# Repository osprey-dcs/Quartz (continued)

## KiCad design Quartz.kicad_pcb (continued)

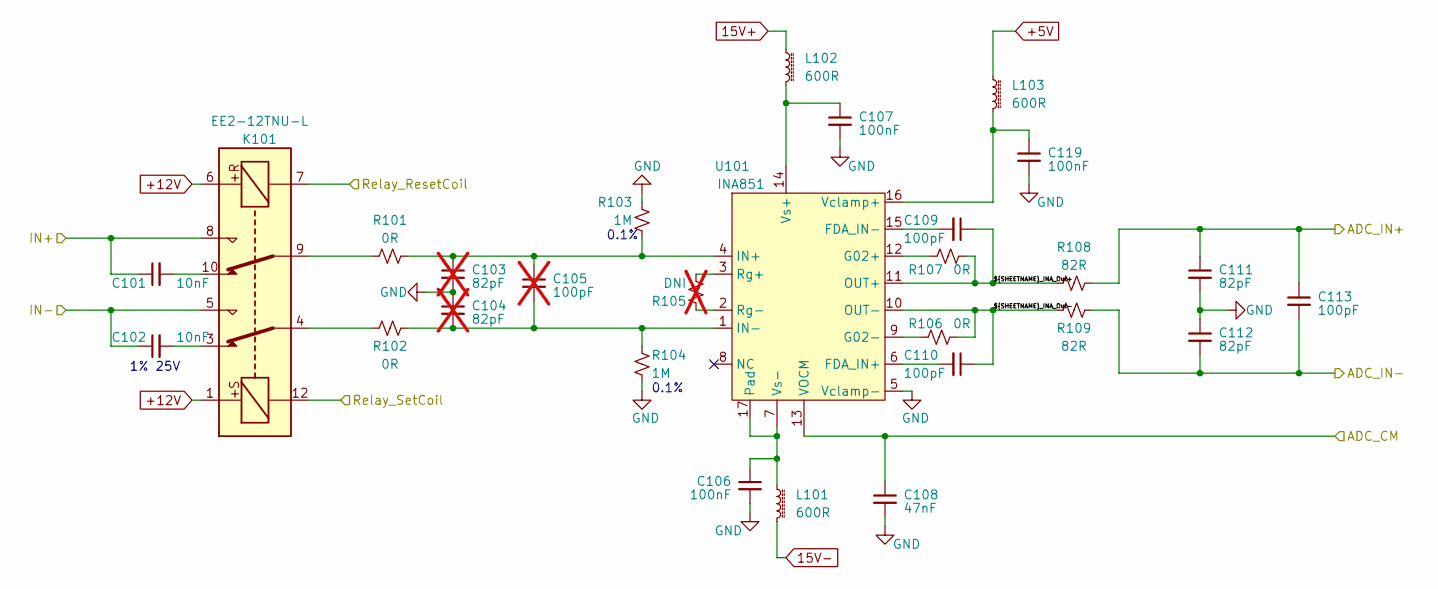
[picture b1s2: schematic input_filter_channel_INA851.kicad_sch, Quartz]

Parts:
C101, C102: 10nF; C_0603_1608Metric; MPN C0603C103F3GAC7867
C103, C104: 82pF; C_0402_1005Metric; MPN DNI; not fitted
C105: 100pF; C_0402_1005Metric; MPN DNI; not fitted
C106, C107, C119: 100nF; C_0402_1005Metric; MPN CL05A104KA5NNNC
C108: 47nF; C_0402_1005Metric; MPN CGA2B3X7R1H473K050BB
C109, C110, C113: 100pF; C_0402_1005Metric; MPN GRM1555C1H101JA01D
C111, C112: 82pF; C_0402_1005Metric; MPN CC0402JRNPO9BN820
K101: EE2-12TNU-L; Relay_DPDT_Kemet_EE2_NU_DoubleCoil; MPN EE2-12TNU-L
L101, L102, L103: 600R; L_0402_1005Metric; MPN BLM15AX601SN1D
R101, R102, R106, R107: 0R; R_0603_1608Metric; MPN ERJ-2GE0R00X
R103, R104: 1M; R_0603_1608Metric; MPN CPF0603B1M0E1
R105: DNI; R_0402_1005Metric; MPN TNPW040211K8BEED; not fitted
R108, R109: 82R; R_0402_1005Metric; MPN RC0402FR-0782RL
U101: INA851; QFN-16-1EP_3x3mm_P0.5mm_EP1.75x1.75mm_ThermalVias; MPN INA851RGTR

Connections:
15V+: L102.1; also elsewhere on the board
15V-: L101.2; also elsewhere on the board
+5V: L103.1; also elsewhere on the board
+12V: K101.1, K101.6; also elsewhere on the board
/ADC1/AIN3+: C111.1, C113.1, R108.2; also elsewhere on the board
/ADC1/AIN3-: C112.2, C113.2, R109.2; also elsewhere on the board
/ADC_VCM1: C108.1, U101.13 (VOCM); also elsewhere on the board
/AIN1+: C101.1, K101.8; also elsewhere on the board
/AIN1-: C102.1, K101.5; also elsewhere on the board
/Channel01/Channel01_INA_Out+: C109.1, R107.2, R108.1, U101.11 (OUT+)
/Channel01/Channel01_INA_Out-: C110.1, R106.2, R109.1, U101.10 (OUT-)
/Relay_ResetCoil1: K101.7; also elsewhere on the board
/Relay_SetCoil1: K101.12; also elsewhere on the board
GND: C103.2, C104.1, C106.2, C107.2, C108.2, C111.2, C112.1, C119.2, R103.1, R104.1, U101.5 (Vclamp-); also elsewhere on the board
unnamed: C101.2, K101.10
unnamed: C102.2, K101.3
unnamed: K101.4, R102.1
unnamed: K101.9, R101.1
unnamed: C110.2, U101.6 (FDA_IN+)
unnamed: C109.2, U101.15 (FDA_IN-)
unnamed: R107.1, U101.12 (G02+)
unnamed: R106.1, U101.9 (G02-)
unnamed: C103.1, C105.1, R101.2, R103.2, U101.4 (IN+)
unnamed: C104.2, C105.2, R102.2, R104.2, U101.1 (IN-)
unnamed: R105.1, U101.3 (Rg+)
unnamed: R105.2, U101.2 (Rg-)
unnamed: C119.1, L103.2, U101.16 (Vclamp+)
unnamed: C107.1, L102.2, U101.14 (Vs+)
unnamed: C106.1, L101.1, U101.7 (Vs-), U101.17 (Pad)

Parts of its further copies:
C201, C202, C301, C302, C401, C402, C501, C502, C601, C602, C701, C702, C801, C802, C901, C902, C1001, C1002, C1101, C1102, C1201, C1202, C1301, C1302, C1401, C1402, C1501, C1502, C1601, C1602, C1701, C1702, C1801, C1802, C1901, C1902, C2001, C2002, C2101, C2102, C2201, C2202, C2301, C2302, C2401, C2402, C2501, C2502, C2601, C2602, C2701, C2702, C2801, C2802, C2901, C2902, C3001, C3002, C3101, C3102, C3201, C3202: 10nF; C_0603_1608Metric; MPN C0603C103F3GAC7867
C203, C204, C303, C304, C403, C404, C503, C504, C603, C604, C703, C704, C803, C804, C903, C904, C1003, C1004, C1103, C1104, C1203, C1204, C1303, C1304, C1403, C1404, C1503, C1504, C1603, C1604, C1703, C1704, C1803, C1804, C1903, C1904, C2003, C2004, C2103, C2104, C2203, C2204, C2303, C2304, C2403, C2404, C2503, C2504, C2603, C2604, C2703, C2704, C2803, C2804, C2903, C2904, C3003, C3004, C3103, C3104, C3203, C3204: 82pF; C_0402_1005Metric; MPN DNI; not fitted
C205, C305, C405, C505, C605, C705, C805, C905, C1005, C1105, C1205, C1305, C1405, C1505, C1605, C1705, C1805, C1905, C2005, C2105, C2205, C2305, C2405, C2505, C2605, C2705, C2805, C2905, C3005, C3105, C3205: 100pF; C_0402_1005Metric; MPN DNI; not fitted
C206, C207, C214, C306, C307, C314, C406, C407, C414, C506, C507, C514, C606, C607, C614, C706, C707, C714, C806, C807, C814, C906, C907, C914, C1006, C1007, C1014, C1106, C1107, C1114, C1206, C1207, C1214, C1306, C1307, C1314, C1406, C1407, C1414, C1506, C1507, C1514, C1606, C1607, C1614, C1706, C1707, C1714, C1806, C1807, C1814, C1906, C1907, C1914, C2006, C2007, C2014, C2106, C2107, C2114, C2206, C2207, C2214, C2306, C2307, C2314, C2406, C2407, C2414, C2506, C2507, C2514, C2606, C2607, C2614, C2706, C2707, C2714, C2806, C2807, C2814, C2906, C2907, C2914, C3006, C3007, C3014, C3106, C3107, C3114, C3206, C3207, C3214: 100nF; C_0402_1005Metric; MPN CL05A104KA5NNNC
C208, C308, C408, C508, C608, C708, C808, C908, C1008, C1108, C1208, C1308, C1408, C1508, C1608, C1708, C1808, C1908, C2008, C2108, C2208, C2308, C2408, C2508, C2608, C2708, C2808, C2908, C3008, C3108, C3208: 47nF; C_0402_1005Metric; MPN CGA2B3X7R1H473K050BB
C209, C210, C213, C309, C310, C313, C409, C410, C413, C509, C510, C513, C609, C610, C613, C709, C710, C713, C809, C810, C813, C909, C910, C913, C1009, C1010, C1013, C1109, C1110, C1113, C1209, C1210, C1213, C1309, C1310, C1313, C1409, C1410, C1413, C1509, C1510, C1513, C1609, C1610, C1613, C1709, C1710, C1713, C1809, C1810, C1813, C1909, C1910, C1913, C2009, C2010, C2013, C2109, C2110, C2113, C2209, C2210, C2213, C2309, C2310, C2313, C2409, C2410, C2413, C2509, C2510, C2513, C2609, C2610, C2613, C2709, C2710, C2713, C2809, C2810, C2813, C2909, C2910, C2913, C3009, C3010, C3013, C3109, C3110, C3113, C3209, C3210, C3213: 100pF; C_0402_1005Metric; MPN GRM1555C1H101JA01D
C211, C212, C311, C312, C411, C412, C511, C512, C611, C612, C711, C712, C811, C812, C911, C912, C1011, C1012, C1111, C1112, C1211, C1212, C1311, C1312, C1411, C1412, C1511, C1512, C1611, C1612, C1711, C1712, C1811, C1812, C1911, C1912, C2011, C2012, C2111, C2112, C2211, C2212, C2311, C2312, C2411, C2412, C2511, C2512, C2611, C2612, C2711, C2712, C2811, C2812, C2911, C2912, C3011, C3012, C3111, C3112, C3211, C3212: 82pF; C_0402_1005Metric; MPN CC0402JRNPO9BN820
K201, K301, K401, K501, K601, K701, K801, K901, K1001, K1101, K1201, K1301, K1401, K1501, K1601, K1701, K1801, K1901, K2001, K2101, K2201, K2301, K2401, K2501, K2601, K2701, K2801, K2901, K3001, K3101, K3201: EE2-12TNU-L; Relay_DPDT_Kemet_EE2_NU_DoubleCoil; MPN EE2-12TNU-L
L201, L202, L203, L301, L302, L303, L401, L402, L403, L501, L502, L503, L601, L602, L603, L701, L702, L703, L801, L802, L803, L901, L902, L903, L1001, L1002, L1003, L1101, L1102, L1103, L1201, L1202, L1203, L1301, L1302, L1303, L1401, L1402, L1403, L1501, L1502, L1503, L1601, L1602, L1603, L1701, L1702, L1703, L1801, L1802, L1803, L1901, L1902, L1903, L2001, L2002, L2003, L2101, L2102, L2103, L2201, L2202, L2203, L2301, L2302, L2303, L2401, L2402, L2403, L2501, L2502, L2503, L2601, L2602, L2603, L2701, L2702, L2703, L2801, L2802, L2803, L2901, L2902, L2903, L3001, L3002, L3003, L3101, L3102, L3103, L3201, L3202, L3203: 600R; L_0402_1005Metric; MPN BLM15AX601SN1D
R201, R202, R206, R207, R301, R302, R306, R307, R401, R402, R406, R407, R501, R502, R506, R507, R601, R602, R606, R607, R701, R702, R706, R707, R801, R802, R806, R807, R901, R902, R906, R907, R1001, R1002, R1006, R1007, R1101, R1102, R1106, R1107, R1201, R1202, R1206, R1207, R1301, R1302, R1306, R1307, R1401, R1402, R1406, R1407, R1501, R1502, R1506, R1507, R1601, R1602, R1606, R1607, R1701, R1702, R1706, R1707, R1801, R1802, R1806, R1807, R1901, R1902, R1906, R1907, R2001, R2002, R2006, R2007, R2101, R2102, R2106, R2107, R2201, R2202, R2206, R2207, R2301, R2302, R2306, R2307, R2401, R2402, R2406, R2407, R2501, R2502, R2506, R2507, R2601, R2602, R2606, R2607, R2701, R2702, R2706, R2707, R2801, R2802, R2806, R2807, R2901, R2902, R2906, R2907, R3001, R3002, R3006, R3007, R3101, R3102, R3106, R3107, R3201, R3202, R3206, R3207: 0R; R_0603_1608Metric; MPN ERJ-2GE0R00X
R203, R204, R303, R304, R403, R404, R503, R504, R603, R604, R703, R704, R803, R804, R903, R904, R1003, R1004, R1103, R1104, R1203, R1204, R1303, R1304, R1403, R1404, R1503, R1504, R1603, R1604, R1703, R1704, R1803, R1804, R1903, R1904, R2003, R2004, R2103, R2104, R2203, R2204, R2303, R2304, R2403, R2404, R2503, R2504, R2603, R2604, R2703, R2704, R2803, R2804, R2903, R2904, R3003, R3004, R3103, R3104, R3203, R3204: 1M; R_0603_1608Metric; MPN CPF0603B1M0E1
R205, R305, R405, R505, R605, R705, R805, R905, R1005, R1105, R1205, R1305, R1405, R1505, R1605, R1705, R1805, R1905, R2005, R2105, R2205, R2305, R2405, R2505, R2605, R2705, R2805, R2905, R3005, R3105, R3205: DNI; R_0402_1005Metric; MPN TNPW040211K8BEED; not fitted
R208, R209, R308, R309, R408, R409, R508, R509, R608, R609, R708, R709, R808, R809, R908, R909, R1008, R1009, R1108, R1109, R1208, R1209, R1308, R1309, R1408, R1409, R1508, R1509, R1608, R1609, R1708, R1709, R1808, R1809, R1908, R1909, R2008, R2009, R2108, R2109, R2208, R2209, R2308, R2309, R2408, R2409, R2508, R2509, R2608, R2609, R2708, R2709, R2808, R2809, R2908, R2909, R3008, R3009, R3108, R3109, R3208, R3209: 82R; R_0402_1005Metric; MPN RC0402FR-0782RL
U201, U301, U401, U501, U601, U701, U801, U901, U1001, U1101, U1201, U1301, U1401, U1501, U1601, U1701, U1801, U1901, U2001, U2101, U2201, U2301, U2401, U2501, U2601, U2701, U2801, U2901, U3001, U3101, U3201: INA851; QFN-16-1EP_3x3mm_P0.5mm_EP1.75x1.75mm_ThermalVias; MPN INA851RGTR

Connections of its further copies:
15V+: L202.1, L302.1, L402.1, L502.1, L602.1, L702.1, L802.1, L902.1, L1002.1, L1102.1, L1202.1, L1302.1, L1402.1, L1502.1, L1602.1, L1702.1, L1802.1, L1902.1, L2002.1, L2102.1, L2202.1, L2302.1, L2402.1, L2502.1, L2602.1, L2702.1, L2802.1, L2902.1, L3002.1, L3102.1, L3202.1; also elsewhere on the board
15V-: L201.2, L301.2, L401.2, L501.2, L601.2, L701.2, L801.2, L901.2, L1001.2, L1101.2, L1201.2, L1301.2, L1401.2, L1501.2, L1601.2, L1701.2, L1801.2, L1901.2, L2001.2, L2101.2, L2201.2, L2301.2, L2401.2, L2501.2, L2601.2, L2701.2, L2801.2, L2901.2, L3001.2, L3101.2, L3201.2; also elsewhere on the board
+5V: L203.1, L303.1, L403.1, L503.1, L603.1, L703.1, L803.1, L903.1, L1003.1, L1103.1, L1203.1, L1303.1, L1403.1, L1503.1, L1603.1, L1703.1, L1803.1, L1903.1, L2003.1, L2103.1, L2203.1, L2303.1, L2403.1, L2503.1, L2603.1, L2703.1, L2803.1, L2903.1, L3003.1, L3103.1, L3203.1; also elsewhere on the board
+12V: K201.1, K201.6, K301.1, K301.6, K401.1, K401.6, K501.1, K501.6, K601.1, K601.6, K701.1, K701.6, K801.1, K801.6, K901.1, K901.6, K1001.1, K1001.6, K1101.1, K1101.6, K1201.1, K1201.6, K1301.1, K1301.6, K1401.1, K1401.6, K1501.1, K1501.6, K1601.1, K1601.6, K1701.1, K1701.6, K1801.1, K1801.6, K1901.1, K1901.6, K2001.1, K2001.6, K2101.1, K2101.6, K2201.1, K2201.6, K2301.1, K2301.6, K2401.1, K2401.6, K2501.1, K2501.6, K2601.1, K2601.6, K2701.1, K2701.6, K2801.1, K2801.6, K2901.1, K2901.6, K3001.1, K3001.6, K3101.1, K3101.6, K3201.1, K3201.6; also elsewhere on the board
/ADC1/AIN0+: C411.1, C413.1, R408.2; also elsewhere on the board
/ADC1/AIN0-: C412.2, C413.2, R409.2; also elsewhere on the board
/ADC1/AIN1+: C311.1, C313.1, R308.2; also elsewhere on the board
/ADC1/AIN1-: C312.2, C313.2, R309.2; also elsewhere on the board
/ADC1/AIN2+: C211.1, C213.1, R208.2; also elsewhere on the board
/ADC1/AIN2-: C212.2, C213.2, R209.2; also elsewhere on the board
/ADC1/AIN4+: C511.1, C513.1, R508.2; also elsewhere on the board
/ADC1/AIN4-: C512.2, C513.2, R509.2; also elsewhere on the board
/ADC1/AIN5+: C611.1, C613.1, R608.2; also elsewhere on the board
/ADC1/AIN5-: C612.2, C613.2, R609.2; also elsewhere on the board
/ADC1/AIN6+: C711.1, C713.1, R708.2; also elsewhere on the board
/ADC1/AIN6-: C712.2, C713.2, R709.2; also elsewhere on the board
/ADC1/AIN7+: C811.1, C813.1, R808.2; also elsewhere on the board
/ADC1/AIN7-: C812.2, C813.2, R809.2; also elsewhere on the board
/ADC2/AIN0+: C1211.1, C1213.1, R1208.2; also elsewhere on the board
/ADC2/AIN0-: C1212.2, C1213.2, R1209.2; also elsewhere on the board
/ADC2/AIN1+: C1111.1, C1113.1, R1108.2; also elsewhere on the board
/ADC2/AIN1-: C1112.2, C1113.2, R1109.2; also elsewhere on the board
/ADC2/AIN2+: C1011.1, C1013.1, R1008.2; also elsewhere on the board
/ADC2/AIN2-: C1012.2, C1013.2, R1009.2; also elsewhere on the board
/ADC2/AIN3+: C911.1, C913.1, R908.2; also elsewhere on the board
/ADC2/AIN3-: C912.2, C913.2, R909.2; also elsewhere on the board
/ADC2/AIN4+: C1311.1, C1313.1, R1308.2; also elsewhere on the board
/ADC2/AIN4-: C1312.2, C1313.2, R1309.2; also elsewhere on the board
/ADC2/AIN5+: C1411.1, C1413.1, R1408.2; also elsewhere on the board
/ADC2/AIN5-: C1412.2, C1413.2, R1409.2; also elsewhere on the board
/ADC2/AIN6+: C1511.1, C1513.1, R1508.2; also elsewhere on the board
/ADC2/AIN6-: C1512.2, C1513.2, R1509.2; also elsewhere on the board
/ADC2/AIN7+: C1611.1, C1613.1, R1608.2; also elsewhere on the board
/ADC2/AIN7-: C1612.2, C1613.2, R1609.2; also elsewhere on the board
/ADC3/AIN0+: C2011.1, C2013.1, R2008.2; also elsewhere on the board
/ADC3/AIN0-: C2012.2, C2013.2, R2009.2; also elsewhere on the board
/ADC3/AIN1+: C1911.1, C1913.1, R1908.2; also elsewhere on the board
/ADC3/AIN1-: C1912.2, C1913.2, R1909.2; also elsewhere on the board
/ADC3/AIN2+: C1811.1, C1813.1, R1808.2; also elsewhere on the board
/ADC3/AIN2-: C1812.2, C1813.2, R1809.2; also elsewhere on the board
/ADC3/AIN3+: C1711.1, C1713.1, R1708.2; also elsewhere on the board
/ADC3/AIN3-: C1712.2, C1713.2, R1709.2; also elsewhere on the board
/ADC3/AIN4+: C2111.1, C2113.1, R2108.2; also elsewhere on the board
/ADC3/AIN4-: C2112.2, C2113.2, R2109.2; also elsewhere on the board
/ADC3/AIN5+: C2211.1, C2213.1, R2208.2; also elsewhere on the board
/ADC3/AIN5-: C2212.2, C2213.2, R2209.2; also elsewhere on the board
/ADC3/AIN6+: C2311.1, C2313.1, R2308.2; also elsewhere on the board
/ADC3/AIN6-: C2312.2, C2313.2, R2309.2; also elsewhere on the board
/ADC3/AIN7+: C2411.1, C2413.1, R2408.2; also elsewhere on the board
/ADC3/AIN7-: C2412.2, C2413.2, R2409.2; also elsewhere on the board
/ADC4/AIN0+: C2811.1, C2813.1, R2808.2; also elsewhere on the board
/ADC4/AIN0-: C2812.2, C2813.2, R2809.2; also elsewhere on the board
/ADC4/AIN1+: C2711.1, C2713.1, R2708.2; also elsewhere on the board
/ADC4/AIN1-: C2712.2, C2713.2, R2709.2; also elsewhere on the board
/ADC4/AIN2+: C2611.1, C2613.1, R2608.2; also elsewhere on the board
/ADC4/AIN2-: C2612.2, C2613.2, R2609.2; also elsewhere on the board
/ADC4/AIN3+: C2511.1, C2513.1, R2508.2; also elsewhere on the board
/ADC4/AIN3-: C2512.2, C2513.2, R2509.2; also elsewhere on the board
/ADC4/AIN4+: C2911.1, C2913.1, R2908.2; also elsewhere on the board
/ADC4/AIN4-: C2912.2, C2913.2, R2909.2; also elsewhere on the board
/ADC4/AIN5+: C3011.1, C3013.1, R3008.2; also elsewhere on the board
/ADC4/AIN5-: C3012.2, C3013.2, R3009.2; also elsewhere on the board
/ADC4/AIN6+: C3111.1, C3113.1, R3108.2; also elsewhere on the board
/ADC4/AIN6-: C3112.2, C3113.2, R3109.2; also elsewhere on the board
/ADC4/AIN7+: C3211.1, C3213.1, R3208.2; also elsewhere on the board
/ADC4/AIN7-: C3212.2, C3213.2, R3209.2; also elsewhere on the board
/ADC_VCM1: C208.1, C308.1, C408.1, C508.1, C608.1, C708.1, C808.1, U201.13 (VOCM), U301.13 (VOCM), U401.13 (VOCM), U501.13 (VOCM), U601.13 (VOCM), U701.13 (VOCM), U801.13 (VOCM); also elsewhere on the board
/ADC_VCM2: C908.1, C1008.1, C1108.1, C1208.1, C1308.1, C1408.1, C1508.1, C1608.1, U901.13 (VOCM), U1001.13 (VOCM), U1101.13 (VOCM), U1201.13 (VOCM), U1301.13 (VOCM), U1401.13 (VOCM), U1501.13 (VOCM), U1601.13 (VOCM); also elsewhere on the board
/ADC_VCM3: C1708.1, C1808.1, C1908.1, C2008.1, C2108.1, C2208.1, C2308.1, C2408.1, U1701.13 (VOCM), U1801.13 (VOCM), U1901.13 (VOCM), U2001.13 (VOCM), U2101.13 (VOCM), U2201.13 (VOCM), U2301.13 (VOCM), U2401.13 (VOCM); also elsewhere on the board
/ADC_VCM4: C2508.1, C2608.1, C2708.1, C2808.1, C2908.1, C3008.1, C3108.1, C3208.1, U2501.13 (VOCM), U2601.13 (VOCM), U2701.13 (VOCM), U2801.13 (VOCM), U2901.13 (VOCM), U3001.13 (VOCM), U3101.13 (VOCM), U3201.13 (VOCM); also elsewhere on the board
/AIN2+: C201.1, K201.8; also elsewhere on the board
/AIN2-: C202.1, K201.5; also elsewhere on the board
/AIN3+: C301.1, K301.8; also elsewhere on the board
/AIN3-: C302.1, K301.5; also elsewhere on the board
/AIN4+: C401.1, K401.8; also elsewhere on the board
/AIN4-: C402.1, K401.5; also elsewhere on the board
/AIN5+: C501.1, K501.8; also elsewhere on the board
/AIN5-: C502.1, K501.5; also elsewhere on the board
/AIN6+: C601.1, K601.8; also elsewhere on the board
/AIN6-: C602.1, K601.5; also elsewhere on the board
/AIN7+: C701.1, K701.8; also elsewhere on the board
/AIN7-: C702.1, K701.5; also elsewhere on the board
/AIN8+: C801.1, K801.8; also elsewhere on the board
/AIN8-: C802.1, K801.5; also elsewhere on the board
/AIN9+: C901.1, K901.8; also elsewhere on the board
/AIN9-: C902.1, K901.5; also elsewhere on the board
/AIN10+: C1001.1, K1001.8; also elsewhere on the board
/AIN10-: C1002.1, K1001.5; also elsewhere on the board
/AIN11+: C1101.1, K1101.8; also elsewhere on the board
/AIN11-: C1102.1, K1101.5; also elsewhere on the board
/AIN12+: C1201.1, K1201.8; also elsewhere on the board
/AIN12-: C1202.1, K1201.5; also elsewhere on the board
/AIN13+: C1301.1, K1301.8; also elsewhere on the board
/AIN13-: C1302.1, K1301.5; also elsewhere on the board
/AIN14+: C1401.1, K1401.8; also elsewhere on the board
/AIN14-: C1402.1, K1401.5; also elsewhere on the board
/AIN15+: C1501.1, K1501.8; also elsewhere on the board
/AIN15-: C1502.1, K1501.5; also elsewhere on the board
/AIN16+: C1601.1, K1601.8; also elsewhere on the board
/AIN16-: C1602.1, K1601.5; also elsewhere on the board
/AIN17+: C1701.1, K1701.8; also elsewhere on the board
/AIN17-: C1702.1, K1701.5; also elsewhere on the board
/AIN18+: C1801.1, K1801.8; also elsewhere on the board
/AIN18-: C1802.1, K1801.5; also elsewhere on the board
/AIN19+: C1901.1, K1901.8; also elsewhere on the board
/AIN19-: C1902.1, K1901.5; also elsewhere on the board
/AIN20+: C2001.1, K2001.8; also elsewhere on the board
/AIN20-: C2002.1, K2001.5; also elsewhere on the board
/AIN21+: C2101.1, K2101.8; also elsewhere on the board
/AIN21-: C2102.1, K2101.5; also elsewhere on the board
/AIN22+: C2201.1, K2201.8; also elsewhere on the board
/AIN22-: C2202.1, K2201.5; also elsewhere on the board
/AIN23+: C2301.1, K2301.8; also elsewhere on the board
/AIN23-: C2302.1, K2301.5; also elsewhere on the board
/AIN24+: C2401.1, K2401.8; also elsewhere on the board
/AIN24-: C2402.1, K2401.5; also elsewhere on the board
/AIN25+: C2501.1, K2501.8; also elsewhere on the board
/AIN25-: C2502.1, K2501.5; also elsewhere on the board
/AIN26+: C2601.1, K2601.8; also elsewhere on the board
/AIN26-: C2602.1, K2601.5; also elsewhere on the board
/AIN27+: C2701.1, K2701.8; also elsewhere on the board
/AIN27-: C2702.1, K2701.5; also elsewhere on the board
/AIN28+: C2801.1, K2801.8; also elsewhere on the board
/AIN28-: C2802.1, K2801.5; also elsewhere on the board
/AIN29+: C2901.1, K2901.8; also elsewhere on the board
/AIN29-: C2902.1, K2901.5; also elsewhere on the board
/AIN30+: C3001.1, K3001.8; also elsewhere on the board
/AIN30-: C3002.1, K3001.5; also elsewhere on the board
/AIN31+: C3101.1, K3101.8; also elsewhere on the board
/AIN31-: C3102.1, K3101.5; also elsewhere on the board
/AIN32+: C3201.1, K3201.8; also elsewhere on the board
/AIN32-: C3202.1, K3201.5; also elsewhere on the board
/Channel02/Channel02_INA_Out+: C209.1, R207.2, R208.1, U201.11 (OUT+)
/Channel02/Channel02_INA_Out-: C210.1, R206.2, R209.1, U201.10 (OUT-)
/Channel03/Channel03_INA_Out+: C309.1, R307.2, R308.1, U301.11 (OUT+)
/Channel03/Channel03_INA_Out-: C310.1, R306.2, R309.1, U301.10 (OUT-)
/Channel04/Channel04_INA_Out+: C409.1, R407.2, R408.1, U401.11 (OUT+)
/Channel04/Channel04_INA_Out-: C410.1, R406.2, R409.1, U401.10 (OUT-)
/Channel05/Channel05_INA_Out+: C509.1, R507.2, R508.1, U501.11 (OUT+)
/Channel05/Channel05_INA_Out-: C510.1, R506.2, R509.1, U501.10 (OUT-)
/Channel06/Channel06_INA_Out+: C609.1, R607.2, R608.1, U601.11 (OUT+)
/Channel06/Channel06_INA_Out-: C610.1, R606.2, R609.1, U601.10 (OUT-)
/Channel07/Channel07_INA_Out+: C709.1, R707.2, R708.1, U701.11 (OUT+)
/Channel07/Channel07_INA_Out-: C710.1, R706.2, R709.1, U701.10 (OUT-)
/Channel08/Channel08_INA_Out+: C809.1, R807.2, R808.1, U801.11 (OUT+)
/Channel08/Channel08_INA_Out-: C810.1, R806.2, R809.1, U801.10 (OUT-)
/Channel09/Channel09_INA_Out+: C909.1, R907.2, R908.1, U901.11 (OUT+)
/Channel09/Channel09_INA_Out-: C910.1, R906.2, R909.1, U901.10 (OUT-)
/Channel10/Channel10_INA_Out+: C1009.1, R1007.2, R1008.1, U1001.11 (OUT+)
/Channel10/Channel10_INA_Out-: C1010.1, R1006.2, R1009.1, U1001.10 (OUT-)
/Channel11/Channel11_INA_Out+: C1109.1, R1107.2, R1108.1, U1101.11 (OUT+)
/Channel11/Channel11_INA_Out-: C1110.1, R1106.2, R1109.1, U1101.10 (OUT-)
/Channel12/Channel12_INA_Out+: C1209.1, R1207.2, R1208.1, U1201.11 (OUT+)
/Channel12/Channel12_INA_Out-: C1210.1, R1206.2, R1209.1, U1201.10 (OUT-)
/Channel13/Channel13_INA_Out+: C1309.1, R1307.2, R1308.1, U1301.11 (OUT+)
/Channel13/Channel13_INA_Out-: C1310.1, R1306.2, R1309.1, U1301.10 (OUT-)
/Channel14/Channel14_INA_Out+: C1409.1, R1407.2, R1408.1, U1401.11 (OUT+)
/Channel14/Channel14_INA_Out-: C1410.1, R1406.2, R1409.1, U1401.10 (OUT-)
/Channel15/Channel15_INA_Out+: C1509.1, R1507.2, R1508.1, U1501.11 (OUT+)
/Channel15/Channel15_INA_Out-: C1510.1, R1506.2, R1509.1, U1501.10 (OUT-)
/Channel16/Channel16_INA_Out+: C1609.1, R1607.2, R1608.1, U1601.11 (OUT+)
/Channel16/Channel16_INA_Out-: C1610.1, R1606.2, R1609.1, U1601.10 (OUT-)
/Channel17/Channel17_INA_Out+: C1709.1, R1707.2, R1708.1, U1701.11 (OUT+)
/Channel17/Channel17_INA_Out-: C1710.1, R1706.2, R1709.1, U1701.10 (OUT-)
/Channel18/Channel18_INA_Out+: C1809.1, R1807.2, R1808.1, U1801.11 (OUT+)
/Channel18/Channel18_INA_Out-: C1810.1, R1806.2, R1809.1, U1801.10 (OUT-)
/Channel19/Channel19_INA_Out+: C1909.1, R1907.2, R1908.1, U1901.11 (OUT+)
/Channel19/Channel19_INA_Out-: C1910.1, R1906.2, R1909.1, U1901.10 (OUT-)
/Channel20/Channel20_INA_Out+: C2009.1, R2007.2, R2008.1, U2001.11 (OUT+)
/Channel20/Channel20_INA_Out-: C2010.1, R2006.2, R2009.1, U2001.10 (OUT-)
/Channel21/Channel21_INA_Out+: C2109.1, R2107.2, R2108.1, U2101.11 (OUT+)
/Channel21/Channel21_INA_Out-: C2110.1, R2106.2, R2109.1, U2101.10 (OUT-)
/Channel22/Channel22_INA_Out+: C2209.1, R2207.2, R2208.1, U2201.11 (OUT+)
/Channel22/Channel22_INA_Out-: C2210.1, R2206.2, R2209.1, U2201.10 (OUT-)
/Channel23/Channel23_INA_Out+: C2309.1, R2307.2, R2308.1, U2301.11 (OUT+)
/Channel23/Channel23_INA_Out-: C2310.1, R2306.2, R2309.1, U2301.10 (OUT-)
/Channel24/Channel24_INA_Out+: C2409.1, R2407.2, R2408.1, U2401.11 (OUT+)
/Channel24/Channel24_INA_Out-: C2410.1, R2406.2, R2409.1, U2401.10 (OUT-)
/Channel25/Channel25_INA_Out+: C2509.1, R2507.2, R2508.1, U2501.11 (OUT+)
/Channel25/Channel25_INA_Out-: C2510.1, R2506.2, R2509.1, U2501.10 (OUT-)
/Channel26/Channel26_INA_Out+: C2609.1, R2607.2, R2608.1, U2601.11 (OUT+)
/Channel26/Channel26_INA_Out-: C2610.1, R2606.2, R2609.1, U2601.10 (OUT-)
/Channel27/Channel27_INA_Out+: C2709.1, R2707.2, R2708.1, U2701.11 (OUT+)
/Channel27/Channel27_INA_Out-: C2710.1, R2706.2, R2709.1, U2701.10 (OUT-)
/Channel28/Channel28_INA_Out+: C2809.1, R2807.2, R2808.1, U2801.11 (OUT+)
/Channel28/Channel28_INA_Out-: C2810.1, R2806.2, R2809.1, U2801.10 (OUT-)
/Channel29/Channel29_INA_Out+: C2909.1, R2907.2, R2908.1, U2901.11 (OUT+)
/Channel29/Channel29_INA_Out-: C2910.1, R2906.2, R2909.1, U2901.10 (OUT-)
/Channel30/Channel30_INA_Out+: C3009.1, R3007.2, R3008.1, U3001.11 (OUT+)
/Channel30/Channel30_INA_Out-: C3010.1, R3006.2, R3009.1, U3001.10 (OUT-)
/Channel31/Channel31_INA_Out+: C3109.1, R3107.2, R3108.1, U3101.11 (OUT+)
/Channel31/Channel31_INA_Out-: C3110.1, R3106.2, R3109.1, U3101.10 (OUT-)
/Channel32/Channel32_INA_Out+: C3209.1, R3207.2, R3208.1, U3201.11 (OUT+)
/Channel32/Channel32_INA_Out-: C3210.1, R3206.2, R3209.1, U3201.10 (OUT-)
/Relay_ResetCoil2: K201.7; also elsewhere on the board
/Relay_ResetCoil3: K301.7; also elsewhere on the board
/Relay_ResetCoil4: K401.7; also elsewhere on the board
/Relay_ResetCoil5: K501.7; also elsewhere on the board
/Relay_ResetCoil6: K601.7; also elsewhere on the board
/Relay_ResetCoil7: K701.7; also elsewhere on the board
/Relay_ResetCoil8: K801.7; also elsewhere on the board
/Relay_ResetCoil9: K901.7; also elsewhere on the board
/Relay_ResetCoil10: K1001.7; also elsewhere on the board
/Relay_ResetCoil11: K1101.7; also elsewhere on the board
/Relay_ResetCoil12: K1201.7; also elsewhere on the board
/Relay_ResetCoil13: K1301.7; also elsewhere on the board
/Relay_ResetCoil14: K1401.7; also elsewhere on the board
/Relay_ResetCoil15: K1501.7; also elsewhere on the board
/Relay_ResetCoil16: K1601.7; also elsewhere on the board
/Relay_ResetCoil17: K1701.7; also elsewhere on the board
/Relay_ResetCoil18: K1801.7; also elsewhere on the board
/Relay_ResetCoil19: K1901.7; also elsewhere on the board
/Relay_ResetCoil20: K2001.7; also elsewhere on the board
/Relay_ResetCoil21: K2101.7; also elsewhere on the board
/Relay_ResetCoil22: K2201.7; also elsewhere on the board
/Relay_ResetCoil23: K2301.7; also elsewhere on the board
/Relay_ResetCoil24: K2401.7; also elsewhere on the board
/Relay_ResetCoil25: K2501.7; also elsewhere on the board
/Relay_ResetCoil26: K2601.7; also elsewhere on the board
/Relay_ResetCoil27: K2701.7; also elsewhere on the board
/Relay_ResetCoil28: K2801.7; also elsewhere on the board
/Relay_ResetCoil29: K2901.7; also elsewhere on the board
/Relay_ResetCoil30: K3001.7; also elsewhere on the board
/Relay_ResetCoil31: K3101.7; also elsewhere on the board
/Relay_ResetCoil32: K3201.7; also elsewhere on the board
/Relay_SetCoil2: K201.12; also elsewhere on the board
/Relay_SetCoil3: K301.12; also elsewhere on the board
/Relay_SetCoil4: K401.12; also elsewhere on the board
/Relay_SetCoil5: K501.12; also elsewhere on the board
/Relay_SetCoil6: K601.12; also elsewhere on the board
/Relay_SetCoil7: K701.12; also elsewhere on the board
/Relay_SetCoil8: K801.12; also elsewhere on the board
/Relay_SetCoil9: K901.12; also elsewhere on the board
/Relay_SetCoil10: K1001.12; also elsewhere on the board
/Relay_SetCoil11: K1101.12; also elsewhere on the board
/Relay_SetCoil12: K1201.12; also elsewhere on the board
/Relay_SetCoil13: K1301.12; also elsewhere on the board
/Relay_SetCoil14: K1401.12; also elsewhere on the board
/Relay_SetCoil15: K1501.12; also elsewhere on the board
/Relay_SetCoil16: K1601.12; also elsewhere on the board
/Relay_SetCoil17: K1701.12; also elsewhere on the board
/Relay_SetCoil18: K1801.12; also elsewhere on the board
/Relay_SetCoil19: K1901.12; also elsewhere on the board
/Relay_SetCoil20: K2001.12; also elsewhere on the board
/Relay_SetCoil21: K2101.12; also elsewhere on the board
/Relay_SetCoil22: K2201.12; also elsewhere on the board
/Relay_SetCoil23: K2301.12; also elsewhere on the board
/Relay_SetCoil24: K2401.12; also elsewhere on the board
/Relay_SetCoil25: K2501.12; also elsewhere on the board
/Relay_SetCoil26: K2601.12; also elsewhere on the board
/Relay_SetCoil27: K2701.12; also elsewhere on the board
/Relay_SetCoil28: K2801.12; also elsewhere on the board
/Relay_SetCoil29: K2901.12; also elsewhere on the board
/Relay_SetCoil30: K3001.12; also elsewhere on the board
/Relay_SetCoil31: K3101.12; also elsewhere on the board
/Relay_SetCoil32: K3201.12; also elsewhere on the board
GND: C203.2, C204.1, C206.2, C207.2, C208.2, C211.2, C212.1, C214.2, C303.2, C304.1, C306.2, C307.2, C308.2, C311.2, C312.1, C314.2, C403.2, C404.1, C406.2, C407.2, C408.2, C411.2, C412.1, C414.2, C503.2, C504.1, C506.2, C507.2, C508.2, C511.2, C512.1, C514.2, C603.2, C604.1, C606.2, C607.2, C608.2, C611.2, C612.1, C614.2, C703.2, C704.1, C706.2, C707.2, C708.2, C711.2, C712.1, C714.2, C803.2, C804.1, C806.2, C807.2, C808.2, C811.2, C812.1, C814.2, C903.2, C904.1, C906.2, C907.2, C908.2, C911.2, C912.1, C914.2, C1003.2, C1004.1, C1006.2, C1007.2, C1008.2, C1011.2, C1012.1, C1014.2, C1103.2, C1104.1, C1106.2, C1107.2, C1108.2, C1111.2, C1112.1, C1114.2, C1203.2, C1204.1, C1206.2, C1207.2, C1208.2, C1211.2, C1212.1, C1214.2, C1303.2, C1304.1, C1306.2, C1307.2, C1308.2, C1311.2, C1312.1, C1314.2, C1403.2, C1404.1, C1406.2, C1407.2, C1408.2, C1411.2, C1412.1, C1414.2, C1503.2, C1504.1, C1506.2, C1507.2, C1508.2, C1511.2, C1512.1, C1514.2, C1603.2, C1604.1, C1606.2, C1607.2, C1608.2, C1611.2, C1612.1, C1614.2, C1703.2, C1704.1, C1706.2, C1707.2, C1708.2, C1711.2, C1712.1, C1714.2, C1803.2, C1804.1, C1806.2, C1807.2, C1808.2, C1811.2, C1812.1, C1814.2, C1903.2, C1904.1, C1906.2, C1907.2, C1908.2, C1911.2, C1912.1, C1914.2, C2003.2, C2004.1, C2006.2, C2007.2, C2008.2, C2011.2, C2012.1, C2014.2, C2103.2, C2104.1, C2106.2, C2107.2, C2108.2, C2111.2, C2112.1, C2114.2, C2203.2, C2204.1, C2206.2, C2207.2, C2208.2, C2211.2, C2212.1, C2214.2, C2303.2, C2304.1, C2306.2, C2307.2, C2308.2, C2311.2, C2312.1, C2314.2, C2403.2, C2404.1, C2406.2, C2407.2, C2408.2, C2411.2, C2412.1, C2414.2, C2503.2, C2504.1, C2506.2, C2507.2, C2508.2, C2511.2, C2512.1, C2514.2, C2603.2, C2604.1, C2606.2, C2607.2, C2608.2, C2611.2, C2612.1, C2614.2, C2703.2, C2704.1, C2706.2, C2707.2, C2708.2, C2711.2, C2712.1, C2714.2, C2803.2, C2804.1, C2806.2, C2807.2, C2808.2, C2811.2, C2812.1, C2814.2, C2903.2, C2904.1, C2906.2, C2907.2, C2908.2, C2911.2, C2912.1, C2914.2, C3003.2, C3004.1, C3006.2, C3007.2, C3008.2, C3011.2, C3012.1, C3014.2, C3103.2, C3104.1, C3106.2, C3107.2, C3108.2, C3111.2, C3112.1, C3114.2, C3203.2, C3204.1, C3206.2, C3207.2, C3208.2, C3211.2, C3212.1, C3214.2, R203.1, R204.1, R303.1, R304.1, R403.1, R404.1, R503.1, R504.1, R603.1, R604.1, R703.1, R704.1, R803.1, R804.1, R903.1, R904.1, R1003.1, R1004.1, R1103.1, R1104.1, R1203.1, R1204.1, R1303.1, R1304.1, R1403.1, R1404.1, R1503.1, R1504.1, R1603.1, R1604.1, R1703.1, R1704.1, R1803.1, R1804.1, R1903.1, R1904.1, R2003.1, R2004.1, R2103.1, R2104.1, R2203.1, R2204.1, R2303.1, R2304.1, R2403.1, R2404.1, R2503.1, R2504.1, R2603.1, R2604.1, R2703.1, R2704.1, R2803.1, R2804.1, R2903.1, R2904.1, R3003.1, R3004.1, R3103.1, R3104.1, R3203.1, R3204.1, U201.5 (Vclamp-), U301.5 (Vclamp-), U401.5 (Vclamp-), U501.5 (Vclamp-)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; also elsewhere on the board
unnamed: C201.2, K201.10
unnamed: C202.2, K201.3
unnamed: C301.2, K301.10
unnamed: C302.2, K301.3
unnamed: C401.2, K401.10
unnamed: C402.2, K401.3
unnamed: C501.2, K501.10
unnamed: C502.2, K501.3
unnamed: C601.2, K601.10
unnamed: C602.2, K601.3
unnamed: C701.2, K701.10
unnamed: C702.2, K701.3
unnamed: C801.2, K801.10
unnamed: C802.2, K801.3
unnamed: C901.2, K901.10
unnamed: C902.2, K901.3
unnamed: C1001.2, K1001.10
unnamed: C1002.2, K1001.3
unnamed: C1101.2, K1101.10
unnamed: C1102.2, K1101.3
unnamed: C1201.2, K1201.10
unnamed: C1202.2, K1201.3
unnamed: C1301.2, K1301.10
unnamed: C1302.2, K1301.3
unnamed: C1401.2, K1401.10
unnamed: C1402.2, K1401.3
unnamed: C1501.2, K1501.10
unnamed: C1502.2, K1501.3
unnamed: C1601.2, K1601.10
unnamed: C1602.2, K1601.3
unnamed: C1701.2, K1701.10
unnamed: C1702.2, K1701.3
unnamed: C1801.2, K1801.10
unnamed: C1802.2, K1801.3
unnamed: C1901.2, K1901.10
unnamed: C1902.2, K1901.3
unnamed: C2001.2, K2001.10
unnamed: C2002.2, K2001.3
unnamed: C2101.2, K2101.10
unnamed: C2102.2, K2101.3
unnamed: C2201.2, K2201.10
unnamed: C2202.2, K2201.3
unnamed: C2301.2, K2301.10
unnamed: C2302.2, K2301.3
unnamed: C2401.2, K2401.10
unnamed: C2402.2, K2401.3
unnamed: C2501.2, K2501.10
unnamed: C2502.2, K2501.3
unnamed: C2601.2, K2601.10
unnamed: C2602.2, K2601.3
unnamed: C2701.2, K2701.10
unnamed: C2702.2, K2701.3
unnamed: C2801.2, K2801.10
unnamed: C2802.2, K2801.3
unnamed: C2901.2, K2901.10
unnamed: C2902.2, K2901.3
unnamed: C3001.2, K3001.10
unnamed: C3002.2, K3001.3
unnamed: C3101.2, K3101.10
unnamed: C3102.2, K3101.3
unnamed: C3201.2, K3201.10
unnamed: C3202.2, K3201.3
unnamed: K201.4, R202.1
unnamed: K201.9, R201.1
unnamed: K301.4, R302.1
unnamed: K301.9, R301.1
unnamed: K401.4, R402.1
unnamed: K401.9, R401.1
unnamed: K501.4, R502.1
unnamed: K501.9, R501.1
unnamed: K601.4, R602.1
unnamed: K601.9, R601.1
unnamed: K701.4, R702.1
unnamed: K701.9, R701.1
unnamed: K801.4, R802.1
unnamed: K801.9, R801.1
unnamed: K901.4, R902.1
unnamed: K901.9, R901.1
unnamed: K1001.4, R1002.1
unnamed: K1001.9, R1001.1
unnamed: K1101.4, R1102.1
unnamed: K1101.9, R1101.1
unnamed: K1201.4, R1202.1
unnamed: K1201.9, R1201.1
unnamed: K1301.4, R1302.1
unnamed: K1301.9, R1301.1
unnamed: K1401.4, R1402.1
unnamed: K1401.9, R1401.1
unnamed: K1501.4, R1502.1
unnamed: K1501.9, R1501.1
unnamed: K1601.4, R1602.1
unnamed: K1601.9, R1601.1
unnamed: K1701.4, R1702.1
unnamed: K1701.9, R1701.1
unnamed: K1801.4, R1802.1
unnamed: K1801.9, R1801.1
unnamed: K1901.4, R1902.1
unnamed: K1901.9, R1901.1
unnamed: K2001.4, R2002.1
unnamed: K2001.9, R2001.1
unnamed: K2101.4, R2102.1
unnamed: K2101.9, R2101.1
unnamed: K2201.4, R2202.1
unnamed: K2201.9, R2201.1
unnamed: K2301.4, R2302.1
unnamed: K2301.9, R2301.1
unnamed: K2401.4, R2402.1
unnamed: K2401.9, R2401.1
unnamed: K2501.4, R2502.1
unnamed: K2501.9, R2501.1
unnamed: K2601.4, R2602.1
unnamed: K2601.9, R2601.1
unnamed: K2701.4, R2702.1
unnamed: K2701.9, R2701.1
unnamed: K2801.4, R2802.1
unnamed: K2801.9, R2801.1
unnamed: K2901.4, R2902.1
unnamed: K2901.9, R2901.1
unnamed: K3001.4, R3002.1
unnamed: K3001.9, R3001.1
unnamed: K3101.4, R3102.1
unnamed: K3101.9, R3101.1
unnamed: K3201.4, R3202.1
unnamed: K3201.9, R3201.1
unnamed: C210.2, U201.6 (FDA_IN+)
unnamed: C209.2, U201.15 (FDA_IN-)
unnamed: R207.1, U201.12 (G02+)
unnamed: R206.1, U201.9 (G02-)
unnamed: C203.1, C205.1, R201.2, R203.2, U201.4 (IN+)
unnamed: C204.2, C205.2, R202.2, R204.2, U201.1 (IN-)
unnamed: R205.1, U201.3 (Rg+)
unnamed: R205.2, U201.2 (Rg-)
unnamed: C214.1, L203.2, U201.16 (Vclamp+)
unnamed: C207.1, L202.2, U201.14 (Vs+)
unnamed: C206.1, L201.1, U201.7 (Vs-), U201.17 (Pad)
unnamed: C310.2, U301.6 (FDA_IN+)
unnamed: C309.2, U301.15 (FDA_IN-)
unnamed: R307.1, U301.12 (G02+)
unnamed: R306.1, U301.9 (G02-)
unnamed: C303.1, C305.1, R301.2, R303.2, U301.4 (IN+)
unnamed: C304.2, C305.2, R302.2, R304.2, U301.1 (IN-)
unnamed: R305.1, U301.3 (Rg+)
unnamed: R305.2, U301.2 (Rg-)
unnamed: C314.1, L303.2, U301.16 (Vclamp+)
unnamed: C307.1, L302.2, U301.14 (Vs+)
unnamed: C306.1, L301.1, U301.7 (Vs-), U301.17 (Pad)
unnamed: C410.2, U401.6 (FDA_IN+)
unnamed: C409.2, U401.15 (FDA_IN-)
unnamed: R407.1, U401.12 (G02+)
unnamed: R406.1, U401.9 (G02-)
unnamed: C403.1, C405.1, R401.2, R403.2, U401.4 (IN+)
unnamed: C404.2, C405.2, R402.2, R404.2, U401.1 (IN-)
unnamed: R405.1, U401.3 (Rg+)
unnamed: R405.2, U401.2 (Rg-)
unnamed: C414.1, L403.2, U401.16 (Vclamp+)
unnamed: C407.1, L402.2, U401.14 (Vs+)
unnamed: C406.1, L401.1, U401.7 (Vs-), U401.17 (Pad)
unnamed: C510.2, U501.6 (FDA_IN+)
unnamed: C509.2, U501.15 (FDA_IN-)
unnamed: R507.1, U501.12 (G02+)
unnamed: R506.1, U501.9 (G02-)
unnamed: C503.1, C505.1, R501.2, R503.2, U501.4 (IN+)
unnamed: C504.2, C505.2, R502.2, R504.2, U501.1 (IN-)
unnamed: R505.1, U501.3 (Rg+)
unnamed: R505.2, U501.2 (Rg-)
unnamed: C514.1, L503.2, U501.16 (Vclamp+)
unnamed: C507.1, L502.2, U501.14 (Vs+)
unnamed: C506.1, L501.1, U501.7 (Vs-), U501.17 (Pad)
unnamed: C610.2, U601.6 (FDA_IN+)
unnamed: C609.2, U601.15 (FDA_IN-)
unnamed: R607.1, U601.12 (G02+)
unnamed: R606.1, U601.9 (G02-)
unnamed: C603.1, C605.1, R601.2, R603.2, U601.4 (IN+)
unnamed: C604.2, C605.2, R602.2, R604.2, U601.1 (IN-)
unnamed: R605.1, U601.3 (Rg+)
unnamed: R605.2, U601.2 (Rg-)
unnamed: C614.1, L603.2, U601.16 (Vclamp+)
unnamed: C607.1, L602.2, U601.14 (Vs+)
unnamed: C606.1, L601.1, U601.7 (Vs-), U601.17 (Pad)
unnamed: C710.2, U701.6 (FDA_IN+)
unnamed: C709.2, U701.15 (FDA_IN-)
unnamed: R707.1, U701.12 (G02+)
unnamed: R706.1, U701.9 (G02-)
unnamed: C703.1, C705.1, R701.2, R703.2, U701.4 (IN+)
unnamed: C704.2, C705.2, R702.2, R704.2, U701.1 (IN-)
unnamed: R705.1, U701.3 (Rg+)
unnamed: R705.2, U701.2 (Rg-)
unnamed: C714.1, L703.2, U701.16 (Vclamp+)
unnamed: C707.1, L702.2, U701.14 (Vs+)
unnamed: C706.1, L701.1, U701.7 (Vs-), U701.17 (Pad)
unnamed: C810.2, U801.6 (FDA_IN+)
unnamed: C809.2, U801.15 (FDA_IN-)
unnamed: R807.1, U801.12 (G02+)
unnamed: R806.1, U801.9 (G02-)
unnamed: C803.1, C805.1, R801.2, R803.2, U801.4 (IN+)
unnamed: C804.2, C805.2, R802.2, R804.2, U801.1 (IN-)
unnamed: R805.1, U801.3 (Rg+)
unnamed: R805.2, U801.2 (Rg-)
unnamed: C814.1, L803.2, U801.16 (Vclamp+)
unnamed: C807.1, L802.2, U801.14 (Vs+)
unnamed: C806.1, L801.1, U801.7 (Vs-), U801.17 (Pad)
unnamed: C910.2, U901.6 (FDA_IN+)
unnamed: C909.2, U901.15 (FDA_IN-)
unnamed: R907.1, U901.12 (G02+)
unnamed: R906.1, U901.9 (G02-)
unnamed: C903.1, C905.1, R901.2, R903.2, U901.4 (IN+)
unnamed: C904.2, C905.2, R902.2, R904.2, U901.1 (IN-)
unnamed: R905.1, U901.3 (Rg+)
unnamed: R905.2, U901.2 (Rg-)
unnamed: C914.1, L903.2, U901.16 (Vclamp+)
unnamed: C907.1, L902.2, U901.14 (Vs+)
unnamed: C906.1, L901.1, U901.7 (Vs-), U901.17 (Pad)
unnamed: C1010.2, U1001.6 (FDA_IN+)
unnamed: C1009.2, U1001.15 (FDA_IN-)
unnamed: R1007.1, U1001.12 (G02+)
unnamed: R1006.1, U1001.9 (G02-)
unnamed: C1003.1, C1005.1, R1001.2, R1003.2, U1001.4 (IN+)
unnamed: C1004.2, C1005.2, R1002.2, R1004.2, U1001.1 (IN-)
unnamed: R1005.1, U1001.3 (Rg+)
unnamed: R1005.2, U1001.2 (Rg-)
unnamed: C1014.1, L1003.2, U1001.16 (Vclamp+)
unnamed: C1007.1, L1002.2, U1001.14 (Vs+)
unnamed: C1006.1, L1001.1, U1001.7 (Vs-), U1001.17 (Pad)
unnamed: C1110.2, U1101.6 (FDA_IN+)
unnamed: C1109.2, U1101.15 (FDA_IN-)
unnamed: R1107.1, U1101.12 (G02+)
unnamed: R1106.1, U1101.9 (G02-)
unnamed: C1103.1, C1105.1, R1101.2, R1103.2, U1101.4 (IN+)
unnamed: C1104.2, C1105.2, R1102.2, R1104.2, U1101.1 (IN-)
unnamed: R1105.1, U1101.3 (Rg+)
unnamed: R1105.2, U1101.2 (Rg-)
unnamed: C1114.1, L1103.2, U1101.16 (Vclamp+)
unnamed: C1107.1, L1102.2, U1101.14 (Vs+)
unnamed: C1106.1, L1101.1, U1101.7 (Vs-), U1101.17 (Pad)
unnamed: C1210.2, U1201.6 (FDA_IN+)
unnamed: C1209.2, U1201.15 (FDA_IN-)
unnamed: R1207.1, U1201.12 (G02+)
unnamed: R1206.1, U1201.9 (G02-)
unnamed: C1203.1, C1205.1, R1201.2, R1203.2, U1201.4 (IN+)
unnamed: C1204.2, C1205.2, R1202.2, R1204.2, U1201.1 (IN-)
unnamed: R1205.1, U1201.3 (Rg+)
unnamed: R1205.2, U1201.2 (Rg-)
unnamed: C1214.1, L1203.2, U1201.16 (Vclamp+)
unnamed: C1207.1, L1202.2, U1201.14 (Vs+)
unnamed: C1206.1, L1201.1, U1201.7 (Vs-), U1201.17 (Pad)
unnamed: C1310.2, U1301.6 (FDA_IN+)
unnamed: C1309.2, U1301.15 (FDA_IN-)
unnamed: R1307.1, U1301.12 (G02+)
unnamed: R1306.1, U1301.9 (G02-)
unnamed: C1303.1, C1305.1, R1301.2, R1303.2, U1301.4 (IN+)
unnamed: C1304.2, C1305.2, R1302.2, R1304.2, U1301.1 (IN-)
unnamed: R1305.1, U1301.3 (Rg+)
unnamed: R1305.2, U1301.2 (Rg-)
unnamed: C1314.1, L1303.2, U1301.16 (Vclamp+)
unnamed: C1307.1, L1302.2, U1301.14 (Vs+)
unnamed: C1306.1, L1301.1, U1301.7 (Vs-), U1301.17 (Pad)
unnamed: C1410.2, U1401.6 (FDA_IN+)
unnamed: C1409.2, U1401.15 (FDA_IN-)
unnamed: R1407.1, U1401.12 (G02+)
unnamed: R1406.1, U1401.9 (G02-)
unnamed: C1403.1, C1405.1, R1401.2, R1403.2, U1401.4 (IN+)
unnamed: C1404.2, C1405.2, R1402.2, R1404.2, U1401.1 (IN-)
unnamed: R1405.1, U1401.3 (Rg+)
unnamed: R1405.2, U1401.2 (Rg-)
unnamed: C1414.1, L1403.2, U1401.16 (Vclamp+)
unnamed: C1407.1, L1402.2, U1401.14 (Vs+)
unnamed: C1406.1, L1401.1, U1401.7 (Vs-), U1401.17 (Pad)
unnamed: C1510.2, U1501.6 (FDA_IN+)
unnamed: C1509.2, U1501.15 (FDA_IN-)
unnamed: R1507.1, U1501.12 (G02+)
unnamed: R1506.1, U1501.9 (G02-)
unnamed: C1503.1, C1505.1, R1501.2, R1503.2, U1501.4 (IN+)
unnamed: C1504.2, C1505.2, R1502.2, R1504.2, U1501.1 (IN-)
unnamed: R1505.1, U1501.3 (Rg+)
unnamed: R1505.2, U1501.2 (Rg-)
unnamed: C1514.1, L1503.2, U1501.16 (Vclamp+)
unnamed: C1507.1, L1502.2, U1501.14 (Vs+)
unnamed: C1506.1, L1501.1, U1501.7 (Vs-), U1501.17 (Pad)
unnamed: C1610.2, U1601.6 (FDA_IN+)
unnamed: C1609.2, U1601.15 (FDA_IN-)
unnamed: R1607.1, U1601.12 (G02+)
unnamed: R1606.1, U1601.9 (G02-)
unnamed: C1603.1, C1605.1, R1601.2, R1603.2, U1601.4 (IN+)
unnamed: C1604.2, C1605.2, R1602.2, R1604.2, U1601.1 (IN-)
unnamed: R1605.1, U1601.3 (Rg+)
unnamed: R1605.2, U1601.2 (Rg-)
unnamed: C1614.1, L1603.2, U1601.16 (Vclamp+)
unnamed: C1607.1, L1602.2, U1601.14 (Vs+)
unnamed: C1606.1, L1601.1, U1601.7 (Vs-), U1601.17 (Pad)
unnamed: C1710.2, U1701.6 (FDA_IN+)
unnamed: C1709.2, U1701.15 (FDA_IN-)
unnamed: R1707.1, U1701.12 (G02+)
unnamed: R1706.1, U1701.9 (G02-)
unnamed: C1703.1, C1705.1, R1701.2, R1703.2, U1701.4 (IN+)
unnamed: C1704.2, C1705.2, R1702.2, R1704.2, U1701.1 (IN-)
unnamed: R1705.1, U1701.3 (Rg+)
unnamed: R1705.2, U1701.2 (Rg-)
unnamed: C1714.1, L1703.2, U1701.16 (Vclamp+)
unnamed: C1707.1, L1702.2, U1701.14 (Vs+)
unnamed: C1706.1, L1701.1, U1701.7 (Vs-), U1701.17 (Pad)
unnamed: C1810.2, U1801.6 (FDA_IN+)
unnamed: C1809.2, U1801.15 (FDA_IN-)
unnamed: R1807.1, U1801.12 (G02+)
unnamed: R1806.1, U1801.9 (G02-)
unnamed: C1803.1, C1805.1, R1801.2, R1803.2, U1801.4 (IN+)
unnamed: C1804.2, C1805.2, R1802.2, R1804.2, U1801.1 (IN-)
unnamed: R1805.1, U1801.3 (Rg+)
unnamed: R1805.2, U1801.2 (Rg-)
unnamed: C1814.1, L1803.2, U1801.16 (Vclamp+)
unnamed: C1807.1, L1802.2, U1801.14 (Vs+)
unnamed: C1806.1, L1801.1, U1801.7 (Vs-), U1801.17 (Pad)
unnamed: C1910.2, U1901.6 (FDA_IN+)
unnamed: C1909.2, U1901.15 (FDA_IN-)
unnamed: R1907.1, U1901.12 (G02+)
unnamed: R1906.1, U1901.9 (G02-)
unnamed: C1903.1, C1905.1, R1901.2, R1903.2, U1901.4 (IN+)
unnamed: C1904.2, C1905.2, R1902.2, R1904.2, U1901.1 (IN-)
unnamed: R1905.1, U1901.3 (Rg+)
unnamed: R1905.2, U1901.2 (Rg-)
unnamed: C1914.1, L1903.2, U1901.16 (Vclamp+)
unnamed: C1907.1, L1902.2, U1901.14 (Vs+)
unnamed: C1906.1, L1901.1, U1901.7 (Vs-), U1901.17 (Pad)
unnamed: C2010.2, U2001.6 (FDA_IN+)
unnamed: C2009.2, U2001.15 (FDA_IN-)
unnamed: R2007.1, U2001.12 (G02+)
unnamed: R2006.1, U2001.9 (G02-)
unnamed: C2003.1, C2005.1, R2001.2, R2003.2, U2001.4 (IN+)
unnamed: C2004.2, C2005.2, R2002.2, R2004.2, U2001.1 (IN-)
unnamed: R2005.1, U2001.3 (Rg+)
unnamed: R2005.2, U2001.2 (Rg-)
unnamed: C2014.1, L2003.2, U2001.16 (Vclamp+)
unnamed: C2007.1, L2002.2, U2001.14 (Vs+)
unnamed: C2006.1, L2001.1, U2001.7 (Vs-), U2001.17 (Pad)
unnamed: C2110.2, U2101.6 (FDA_IN+)
unnamed: C2109.2, U2101.15 (FDA_IN-)
unnamed: R2107.1, U2101.12 (G02+)
unnamed: R2106.1, U2101.9 (G02-)
unnamed: C2103.1, C2105.1, R2101.2, R2103.2, U2101.4 (IN+)
unnamed: C2104.2, C2105.2, R2102.2, R2104.2, U2101.1 (IN-)
unnamed: R2105.1, U2101.3 (Rg+)
unnamed: R2105.2, U2101.2 (Rg-)
unnamed: C2114.1, L2103.2, U2101.16 (Vclamp+)
unnamed: C2107.1, L2102.2, U2101.14 (Vs+)
unnamed: C2106.1, L2101.1, U2101.7 (Vs-), U2101.17 (Pad)
unnamed: C2210.2, U2201.6 (FDA_IN+)
unnamed: C2209.2, U2201.15 (FDA_IN-)
unnamed: R2207.1, U2201.12 (G02+)
unnamed: R2206.1, U2201.9 (G02-)
unnamed: C2203.1, C2205.1, R2201.2, R2203.2, U2201.4 (IN+)
unnamed: C2204.2, C2205.2, R2202.2, R2204.2, U2201.1 (IN-)
unnamed: R2205.1, U2201.3 (Rg+)
unnamed: R2205.2, U2201.2 (Rg-)
unnamed: C2214.1, L2203.2, U2201.16 (Vclamp+)
unnamed: C2207.1, L2202.2, U2201.14 (Vs+)
unnamed: C2206.1, L2201.1, U2201.7 (Vs-), U2201.17 (Pad)
unnamed: C2310.2, U2301.6 (FDA_IN+)
unnamed: C2309.2, U2301.15 (FDA_IN-)
unnamed: R2307.1, U2301.12 (G02+)
unnamed: R2306.1, U2301.9 (G02-)
unnamed: C2303.1, C2305.1, R2301.2, R2303.2, U2301.4 (IN+)
unnamed: C2304.2, C2305.2, R2302.2, R2304.2, U2301.1 (IN-)
unnamed: R2305.1, U2301.3 (Rg+)
unnamed: R2305.2, U2301.2 (Rg-)
unnamed: C2314.1, L2303.2, U2301.16 (Vclamp+)
unnamed: C2307.1, L2302.2, U2301.14 (Vs+)
unnamed: C2306.1, L2301.1, U2301.7 (Vs-), U2301.17 (Pad)
unnamed: C2410.2, U2401.6 (FDA_IN+)
unnamed: C2409.2, U2401.15 (FDA_IN-)
unnamed: R2407.1, U2401.12 (G02+)
unnamed: R2406.1, U2401.9 (G02-)
unnamed: C2403.1, C2405.1, R2401.2, R2403.2, U2401.4 (IN+)
unnamed: C2404.2, C2405.2, R2402.2, R2404.2, U2401.1 (IN-)
unnamed: R2405.1, U2401.3 (Rg+)
unnamed: R2405.2, U2401.2 (Rg-)
unnamed: C2414.1, L2403.2, U2401.16 (Vclamp+)
unnamed: C2407.1, L2402.2, U2401.14 (Vs+)
unnamed: C2406.1, L2401.1, U2401.7 (Vs-), U2401.17 (Pad)
unnamed: C2510.2, U2501.6 (FDA_IN+)
unnamed: C2509.2, U2501.15 (FDA_IN-)
unnamed: R2507.1, U2501.12 (G02+)
unnamed: R2506.1, U2501.9 (G02-)
unnamed: C2503.1, C2505.1, R2501.2, R2503.2, U2501.4 (IN+)
unnamed: C2504.2, C2505.2, R2502.2, R2504.2, U2501.1 (IN-)
unnamed: R2505.1, U2501.3 (Rg+)
unnamed: R2505.2, U2501.2 (Rg-)
unnamed: C2514.1, L2503.2, U2501.16 (Vclamp+)
unnamed: C2507.1, L2502.2, U2501.14 (Vs+)
unnamed: C2506.1, L2501.1, U2501.7 (Vs-), U2501.17 (Pad)
unnamed: C2610.2, U2601.6 (FDA_IN+)
unnamed: C2609.2, U2601.15 (FDA_IN-)
unnamed: R2607.1, U2601.12 (G02+)
unnamed: R2606.1, U2601.9 (G02-)
unnamed: C2603.1, C2605.1, R2601.2, R2603.2, U2601.4 (IN+)
unnamed: C2604.2, C2605.2, R2602.2, R2604.2, U2601.1 (IN-)
unnamed: R2605.1, U2601.3 (Rg+)
unnamed: R2605.2, U2601.2 (Rg-)
unnamed: C2614.1, L2603.2, U2601.16 (Vclamp+)
unnamed: C2607.1, L2602.2, U2601.14 (Vs+)
unnamed: C2606.1, L2601.1, U2601.7 (Vs-), U2601.17 (Pad)
unnamed: C2710.2, U2701.6 (FDA_IN+)
unnamed: C2709.2, U2701.15 (FDA_IN-)
unnamed: R2707.1, U2701.12 (G02+)
unnamed: R2706.1, U2701.9 (G02-)
unnamed: C2703.1, C2705.1, R2701.2, R2703.2, U2701.4 (IN+)
unnamed: C2704.2, C2705.2, R2702.2, R2704.2, U2701.1 (IN-)
unnamed: R2705.1, U2701.3 (Rg+)
unnamed: R2705.2, U2701.2 (Rg-)
unnamed: C2714.1, L2703.2, U2701.16 (Vclamp+)
unnamed: C2707.1, L2702.2, U2701.14 (Vs+)
unnamed: C2706.1, L2701.1, U2701.7 (Vs-), U2701.17 (Pad)
unnamed: C2810.2, U2801.6 (FDA_IN+)
unnamed: C2809.2, U2801.15 (FDA_IN-)
unnamed: R2807.1, U2801.12 (G02+)
unnamed: R2806.1, U2801.9 (G02-)
unnamed: C2803.1, C2805.1, R2801.2, R2803.2, U2801.4 (IN+)
unnamed: C2804.2, C2805.2, R2802.2, R2804.2, U2801.1 (IN-)
unnamed: R2805.1, U2801.3 (Rg+)
unnamed: R2805.2, U2801.2 (Rg-)
unnamed: C2814.1, L2803.2, U2801.16 (Vclamp+)
unnamed: C2807.1, L2802.2, U2801.14 (Vs+)
unnamed: C2806.1, L2801.1, U2801.7 (Vs-), U2801.17 (Pad)
unnamed: C2910.2, U2901.6 (FDA_IN+)
unnamed: C2909.2, U2901.15 (FDA_IN-)
unnamed: R2907.1, U2901.12 (G02+)
unnamed: R2906.1, U2901.9 (G02-)
unnamed: C2903.1, C2905.1, R2901.2, R2903.2, U2901.4 (IN+)
unnamed: C2904.2, C2905.2, R2902.2, R2904.2, U2901.1 (IN-)
unnamed: R2905.1, U2901.3 (Rg+)
unnamed: R2905.2, U2901.2 (Rg-)
unnamed: C2914.1, L2903.2, U2901.16 (Vclamp+)
unnamed: C2907.1, L2902.2, U2901.14 (Vs+)
unnamed: C2906.1, L2901.1, U2901.7 (Vs-), U2901.17 (Pad)
unnamed: C3010.2, U3001.6 (FDA_IN+)
unnamed: C3009.2, U3001.15 (FDA_IN-)
unnamed: R3007.1, U3001.12 (G02+)
unnamed: R3006.1, U3001.9 (G02-)
unnamed: C3003.1, C3005.1, R3001.2, R3003.2, U3001.4 (IN+)
unnamed: C3004.2, C3005.2, R3002.2, R3004.2, U3001.1 (IN-)
unnamed: R3005.1, U3001.3 (Rg+)
unnamed: R3005.2, U3001.2 (Rg-)
unnamed: C3014.1, L3003.2, U3001.16 (Vclamp+)
unnamed: C3007.1, L3002.2, U3001.14 (Vs+)
unnamed: C3006.1, L3001.1, U3001.7 (Vs-), U3001.17 (Pad)
unnamed: C3110.2, U3101.6 (FDA_IN+)
unnamed: C3109.2, U3101.15 (FDA_IN-)
unnamed: R3107.1, U3101.12 (G02+)
unnamed: R3106.1, U3101.9 (G02-)
unnamed: C3103.1, C3105.1, R3101.2, R3103.2, U3101.4 (IN+)
unnamed: C3104.2, C3105.2, R3102.2, R3104.2, U3101.1 (IN-)
unnamed: R3105.1, U3101.3 (Rg+)
unnamed: R3105.2, U3101.2 (Rg-)
unnamed: C3114.1, L3103.2, U3101.16 (Vclamp+)
unnamed: C3107.1, L3102.2, U3101.14 (Vs+)
unnamed: C3106.1, L3101.1, U3101.7 (Vs-), U3101.17 (Pad)
unnamed: C3210.2, U3201.6 (FDA_IN+)
unnamed: C3209.2, U3201.15 (FDA_IN-)
unnamed: R3207.1, U3201.12 (G02+)
unnamed: R3206.1, U3201.9 (G02-)
unnamed: C3203.1, C3205.1, R3201.2, R3203.2, U3201.4 (IN+)
unnamed: C3204.2, C3205.2, R3202.2, R3204.2, U3201.1 (IN-)
unnamed: R3205.1, U3201.3 (Rg+)
unnamed: R3205.2, U3201.2 (Rg-)
unnamed: C3214.1, L3203.2, U3201.16 (Vclamp+)
unnamed: C3207.1, L3202.2, U3201.14 (Vs+)
unnamed: C3206.1, L3201.1, U3201.7 (Vs-), U3201.17 (Pad)

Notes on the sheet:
1% 25V
0.1%
